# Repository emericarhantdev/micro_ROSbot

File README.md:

# PAMI Power Board (KiCad)

Power/IO board for a Small MicroROS-based robot project. Contains KiCad schematics/PCB, custom symbols/footprints, and fabrication outputs (Gerbers + drills).

## Contents
- PAMI-Power_Board.kicad_pro / .kicad_sch / .kicad_pcb: main KiCad project
- FAB/: manufacturing files (Gerbers, PTH/NPTH drills, job file)
- Specific_symbols_and_footprints/: custom symbols/footprints + 3D models
- top_level_diagrams/: high-level diagrams

## Board routing stage

## Final board result

## Fabrication
Upload the files in FAB/ (Gerbers + drills) to your PCB manufacturer.

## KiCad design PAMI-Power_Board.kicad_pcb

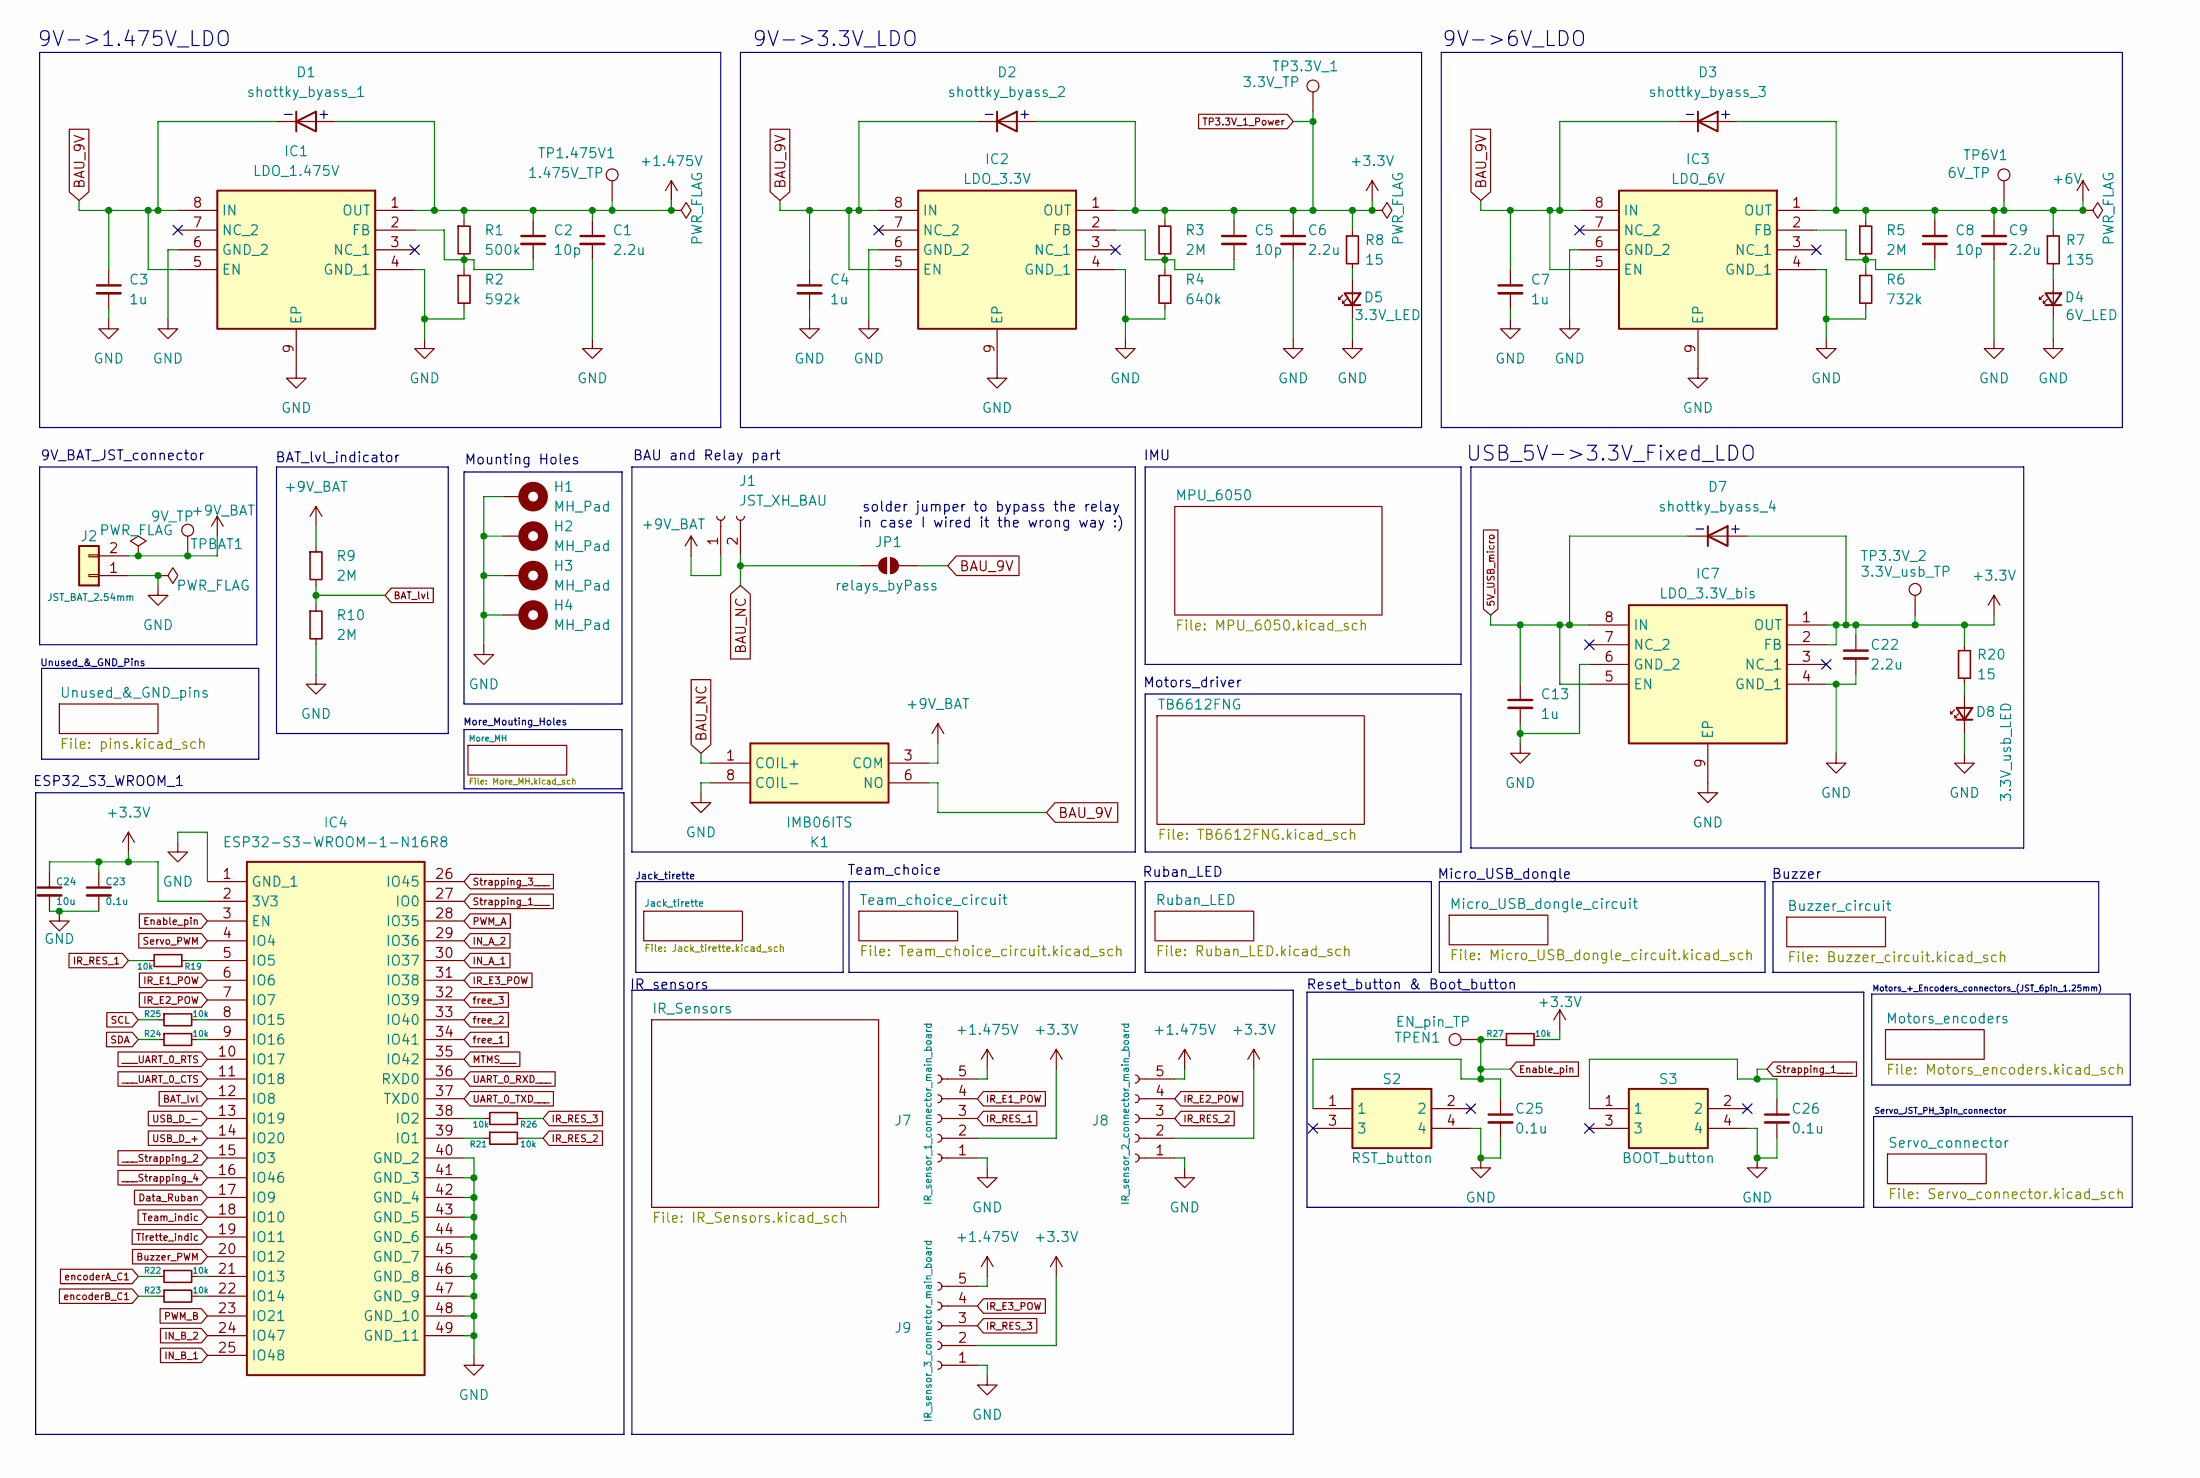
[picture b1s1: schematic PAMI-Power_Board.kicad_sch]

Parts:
C1, C6, C9, C22: 2.2u; C_0805_2012Metric_Pad1.18x1.45mm_HandSolder
C2, C5, C8: 10p; C_0805_2012Metric_Pad1.18x1.45mm_HandSolder
C3, C4, C7, C13: 1u; C_0805_2012Metric_Pad1.18x1.45mm_HandSolder
C23, C25, C26: 0.1u; C_0805_2012Metric_Pad1.18x1.45mm_HandSolder
C24: 10u; C_0805_2012Metric_Pad1.18x1.45mm_HandSolder
D1: shottky_byass_1; SOD2512X113N
D2: shottky_byass_2; SOD2512X113N
D3: shottky_byass_3; SOD2512X113N
D4: 6V_LED; ASCKCG00NW5X5020302
D5: 3.3V_LED; ASCKCG00NW5X5020302
D7: shottky_byass_4; SOD2512X113N
D8: 3.3V_usb_LED; ASCKCG00NW5X5020302
H1, H2, H3, H4: MH_Pad; MountingHole_2.2mm_M2_Pad_Via
IC1: LDO_1.475V; SOP65P490X110-9N; Manufacturer_Part_Number TLV76701DGNR; Mouser Part Number 595-TLV76701DGNR
IC2: LDO_3.3V; SOP65P490X110-9N; Manufacturer_Part_Number TLV76701DGNR; Mouser Part Number 595-TLV76701DGNR
IC3: LDO_6V; SOP65P490X110-9N; Manufacturer_Part_Number TLV76701DGNR; Mouser Part Number 595-TLV76701DGNR
IC4: ESP32-S3-WROOM-1-N16R8; ESP32S3WROOM1N16R8; Manufacturer_Part_Number ESP32-S3-WROOM-1-N16R8; Mouser Part Number 356-ESP32S3WRM1N16R8
IC7: LDO_3.3V_bis; SOP65P490X110-9N; Manufacturer_Part_Number TLV76701DGNR; Mouser Part Number 595-TLV76701DGNR
J1: JST_XH_BAU; JST_XH_B2B-XH-A_1x02_P2.50mm_Vertical
J2: JST_BAT_2.54mm; JST_XH_B2B-XH-A_1x02_P2.50mm_Vertical
J7: IR_sensor_1_connector_main_board; JST_ZH_1x05_P1.50mm_Vertical
J8: IR_sensor_2_connector_main_board; JST_ZH_1x05_P1.50mm_Vertical
J9: IR_sensor_3_connector_main_board; JST_ZH_1x05_P1.50mm_Vertical
JP1: relays_byPass; SolderJumper-2_P1.3mm_Open_Pad1.0x1.5mm
K1: IMB06ITS; IMB03ITS; Manufacturer_Part_Number IMB03ITS; Mouser Part Number 655-IMB03ITS
R1: 500k; R_0805_2012Metric_Pad1.20x1.40mm_HandSolder
R2: 592k; R_0805_2012Metric_Pad1.20x1.40mm_HandSolder
R3, R5, R9, R10: 2M; R_0805_2012Metric_Pad1.20x1.40mm_HandSolder
R4: 640k; R_0805_2012Metric_Pad1.20x1.40mm_HandSolder
R6: 732k; R_0805_2012Metric_Pad1.20x1.40mm_HandSolder
R7: 135; R_0805_2012Metric_Pad1.20x1.40mm_HandSolder
R8, R20: 15; R_0805_2012Metric_Pad1.20x1.40mm_HandSolder
R19, R21, R22, R23, R24, R25, R26, R27: 10k; R_0805_2012Metric_Pad1.20x1.40mm_HandSolder
S2: RST_button; PTS810SJG250SMTRLFS; Manufacturer_Part_Number PTS810SJM250SMTRLFS; Mouser Part Number 611-PTS810SJM250SMTR
S3: BOOT_button; PTS810SJG250SMTRLFS; Manufacturer_Part_Number PTS810SJM250SMTRLFS; Mouser Part Number 611-PTS810SJM250SMTR
TP1.475V1: 1.475V_TP; S275146R
TP3.3V_1: 3.3V_TP; S275146R
TP3.3V_2: 3.3V_usb_TP; S275146R
TP6V1: 6V_TP; S275146R
TPBAT1: 9V_TP; S275146R
TPEN1: EN_pin_TP; S275146R

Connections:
5V_USB_micro: C13.1, D7.1 (K), IC7.5 (EN), IC7.8 (IN); also elsewhere on the board
+1.475V: C1.1, C2.1, D1.2 (A), IC1.1 (OUT), J7.5, J8.5, J9.5, R1.1, TP1.475V1.1; also elsewhere on the board
+6V: C8.1, C9.1, D3.2 (A), IC3.1 (OUT), R5.1, R7.1, TP6V1.1; also elsewhere on the board
+9V_BAT: J1.1, J2.2, K1.3 (COM), R9.1, TPBAT1.1
BAT_lvl: IC4.12 (IO8), R9.2, R10.1
BAU_9V: C3.1, C4.1, C7.1, D1.1 (K), D2.1 (K), D3.1 (K), IC1.5 (EN), IC1.8 (IN), IC2.5 (EN), IC2.8 (IN), IC3.5 (EN), IC3.8 (IN), JP1.2 (B), K1.6 (NO)
BAU_NC: J1.2, JP1.1 (A), K1.1 (COIL+)
Buzzer_PWM: IC4.20 (IO12); also elsewhere on the board
Data_Ruban: IC4.17 (IO9); also elsewhere on the board
Enable_pin: C25.1, IC4.3 (EN), R27.1, S2.1, TPEN1.1
GND: C1.2, C3.2, C4.2, C6.2, C7.2, C9.2, C13.2, C22.2, C23.2, C24.2, C25.2, C26.2, D4.1 (K), D5.1 (K), D8.1 (K), H1.1, H2.1, H3.1, H4.1, IC1.4 (GND_1), IC1.6 (GND_2), IC1.9 (EP), IC2.4 (GND_1), IC2.6 (GND_2), IC2.9 (EP), IC3.4 (GND_1), IC3.6 (GND_2), IC3.9 (EP), IC4.1 (GND_1), IC4.40 (GND_2), IC4.41 (GND_3), IC4.42 (GND_4), IC4.43 (GND_5), IC4.44 (GND_6), IC4.45 (GND_7), IC4.46 (GND_8), IC4.47 (GND_9), IC4.48 (GND_10), IC4.49 (GND_11), IC7.4 (GND_1), IC7.6 (GND_2), IC7.9 (EP), J2.1, J7.1, J8.1, J9.1, K1.8 (COIL-), R2.2, R4.2, R6.2, R10.2, S2.4, S3.4; also elsewhere on the board
IN_A_1: IC4.30 (IO37); also elsewhere on the board
IN_A_2: IC4.29 (IO36); also elsewhere on the board
IN_B_1: IC4.25 (IO48); also elsewhere on the board
IN_B_2: IC4.24 (IO47); also elsewhere on the board
IR_E1_POW: IC4.6 (IO6), J7.4; also elsewhere on the board
IR_E2_POW: IC4.7 (IO7), J8.4; also elsewhere on the board
IR_E3_POW: IC4.31 (IO38), J9.4; also elsewhere on the board
IR_RES_1: J7.3, R19.2; also elsewhere on the board
IR_RES_2: J8.3, R21.2; also elsewhere on the board
IR_RES_3: J9.3, R26.1; also elsewhere on the board
MTMS___: IC4.35 (IO42); also elsewhere on the board
unnamed: D4.2 (A), R7.2
unnamed: D5.2 (A), R8.2
unnamed: D8.2 (A), R20.2
unnamed: C2.2, IC1.2 (FB), R1.2, R2.1
unnamed: C5.2, IC2.2 (FB), R3.2, R4.1
unnamed: C8.2, IC3.2 (FB), R5.2, R6.1
unnamed: IC4.39 (IO1), R21.1
unnamed: IC4.38 (IO2), R26.2
unnamed: IC4.5 (IO5), R19.1
unnamed: IC4.21 (IO13), R22.2
unnamed: IC4.22 (IO14), R23.2
unnamed: IC4.8 (IO15), R25.2
unnamed: IC4.9 (IO16), R24.2
PWM_A: IC4.28 (IO35); also elsewhere on the board
PWM_B: IC4.23 (IO21); also elsewhere on the board
SCL: R25.1; also elsewhere on the board
SDA: R24.1; also elsewhere on the board
Servo_PWM: IC4.4 (IO4); also elsewhere on the board
Strapping_1___: C26.1, IC4.27 (IO0), S3.1
Strapping_3___: IC4.26 (IO45); also elsewhere on the board
TP3.3V_1_Power: C5.1, C6.1, C22.1, C23.1, C24.1, D2.2 (A), D7.2 (A), IC2.1 (OUT), IC4.2 (3V3), IC7.1 (OUT), IC7.2 (FB), J7.2, J8.2, J9.2, R3.1, R8.1, R20.1, R27.2, TP3.3V_1.1, TP3.3V_2.1; also elsewhere on the board
Team_indic: IC4.18 (IO10); also elsewhere on the board
Tirette_indic: IC4.19 (IO11); also elsewhere on the board
UART_0_RXD___: IC4.36 (RXD0); also elsewhere on the board
UART_0_TXD___: IC4.37 (TXD0); also elsewhere on the board
USB_D_+: IC4.14 (IO20); also elsewhere on the board
USB_D_-: IC4.13 (IO19); also elsewhere on the board
___Strapping_2: IC4.15 (IO3); also elsewhere on the board
___Strapping_4: IC4.16 (IO46); also elsewhere on the board
___UART_0_CTS: IC4.11 (IO18); also elsewhere on the board
___UART_0_RTS: IC4.10 (IO17); also elsewhere on the board
encoderA_C1: R22.1; also elsewhere on the board
encoderB_C1: R23.1; also elsewhere on the board
free_1: IC4.34 (IO41); also elsewhere on the board
free_2: IC4.33 (IO40); also elsewhere on the board
free_3: IC4.32 (IO39); also elsewhere on the board

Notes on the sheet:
9V->6V_LDO
Motors_driver
USB_5V->3.3V_Fixed_LDO
Servo_JST_PH_3pin_connector
solder jumper to bypass the relay in case I wired it the wrong way :)
Ruban_LED
BAU and Relay part
IR_sensors
9V->1.475V_LDO
IMU
9V_BAT_JST_connector
Team_choice
ESP32_S3_WROOM_1
Jack_tirette
Motors_+_Encoders_connectors_(JST_6pin_1.25mm)
Mounting Holes
9V->3.3V_LDO
Micro_USB_dongle
BAT_lvl_indicator
Buzzer
More_Mouting_Holes
Unused_&_GND_Pins
Reset_button & Boot_button

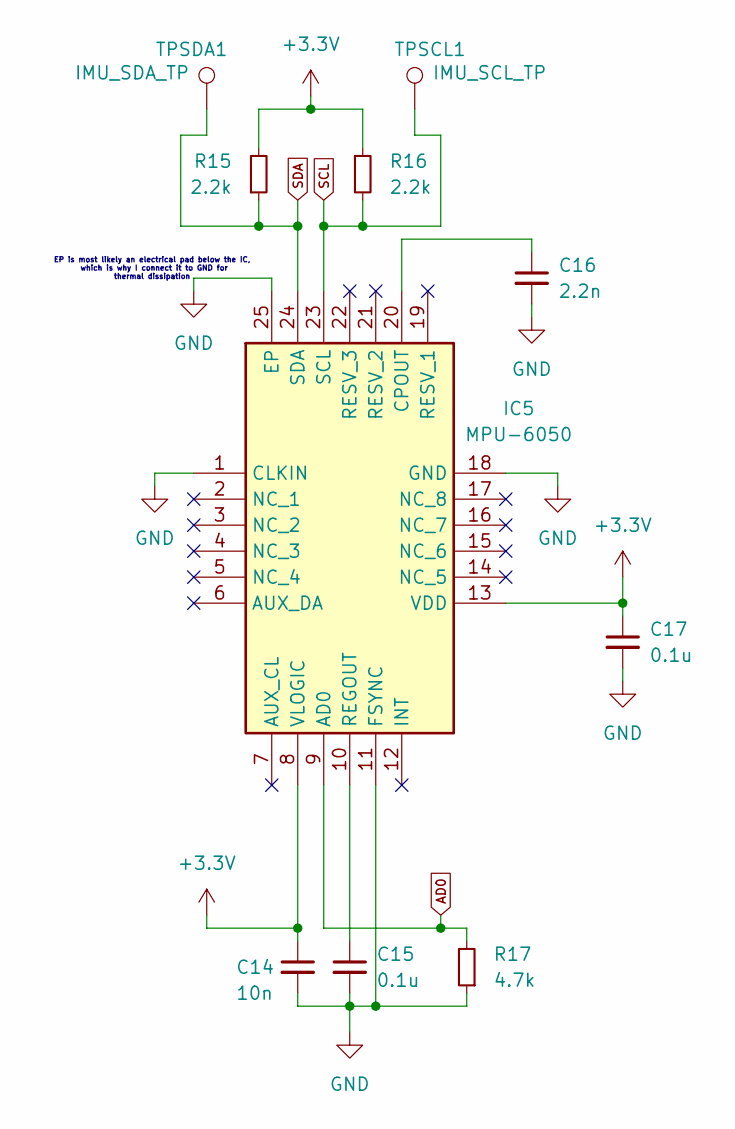
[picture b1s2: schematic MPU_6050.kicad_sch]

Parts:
C14: 10n; C_0805_2012Metric_Pad1.18x1.45mm_HandSolder
C15, C17: 0.1u; C_0805_2012Metric_Pad1.18x1.45mm_HandSolder
C16: 2.2n; C_0805_2012Metric_Pad1.18x1.45mm_HandSolder
IC5: MPU-6050; MPU6050; Manufacturer_Part_Number MPU-6050; Mouser Part Number 410-MPU-6050
R15, R16: 2.2k; R_0805_2012Metric_Pad1.20x1.40mm_HandSolder
R17: 4.7k; R_0805_2012Metric_Pad1.20x1.40mm_HandSolder
TPSCL1: IMU_SCL_TP; S275146R
TPSDA1: IMU_SDA_TP; S275146R

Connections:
AD0: IC5.9 (AD0), R17.2
GND: C14.2, C15.2, C16.2, C17.2, IC5.1 (CLKIN), IC5.11 (FSYNC), IC5.18 (GND), IC5.25 (EP), R17.1; also elsewhere on the board
unnamed: C16.1, IC5.20 (CPOUT)
unnamed: C15.1, IC5.10 (REGOUT)
SCL: IC5.23 (SCL), R16.2, TPSCL1.1; also elsewhere on the board
SDA: IC5.24 (SDA), R15.1, TPSDA1.1; also elsewhere on the board
TP3.3V_1_Power: C14.1, C17.1, IC5.8 (VLOGIC), IC5.13 (VDD), R15.2, R16.1; also elsewhere on the board

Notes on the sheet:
EP is most likely an electrical pad below the IC, which is why I connect it to GND for thermal dissipation

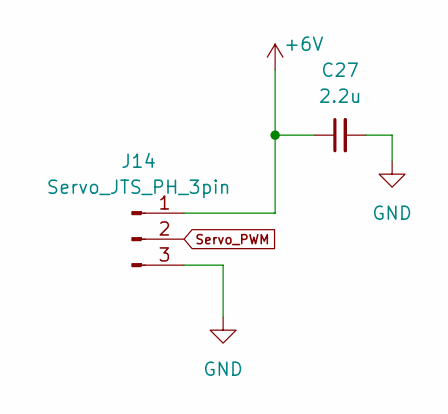
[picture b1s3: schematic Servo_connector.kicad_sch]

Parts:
C27: 2.2u; C_0805_2012Metric_Pad1.18x1.45mm_HandSolder
J14: Servo_JTS_PH_3pin; JST_PH_B3B-PH-K_1x03_P2.00mm_Vertical

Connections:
+6V: C27.1, J14.1; also elsewhere on the board
GND: C27.2, J14.3; also elsewhere on the board
Servo_PWM: J14.2; also elsewhere on the board

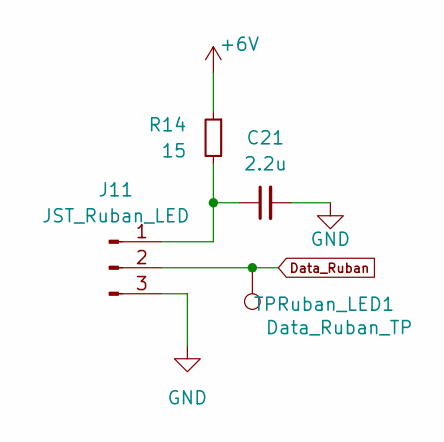
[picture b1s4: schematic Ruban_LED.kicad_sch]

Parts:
C21: 2.2u; C_0805_2012Metric_Pad1.18x1.45mm_HandSolder
J11: JST_Ruban_LED; JST_PH_B3B-PH-K_1x03_P2.00mm_Vertical
R14: 15; R_0805_2012Metric_Pad1.20x1.40mm_HandSolder
TPRuban_LED1: Data_Ruban_TP; S275146R

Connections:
+6V: R14.1; also elsewhere on the board
Data_Ruban: J11.2, TPRuban_LED1.1; also elsewhere on the board
GND: C21.2, J11.3; also elsewhere on the board
unnamed: C21.1, J11.1, R14.2

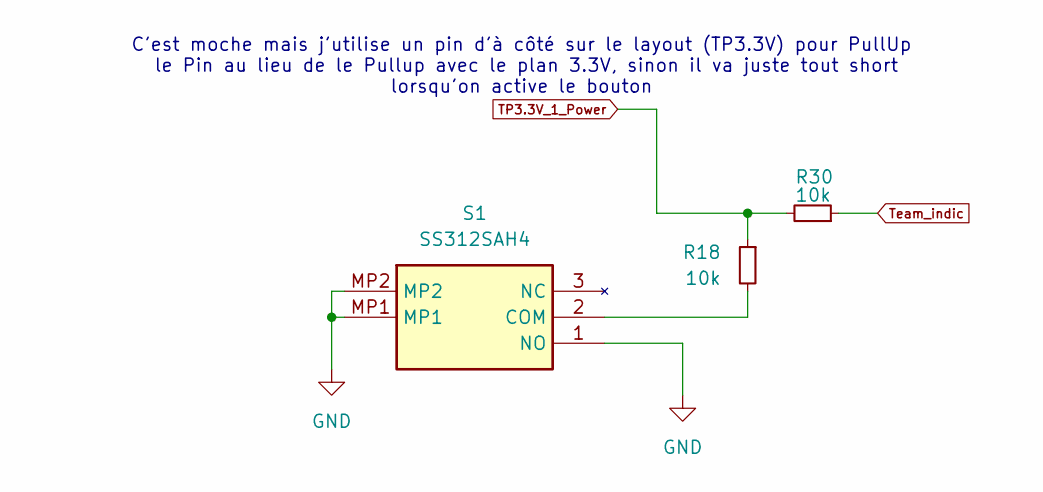
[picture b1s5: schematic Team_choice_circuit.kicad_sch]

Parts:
R18, R30: 10k; R_0805_2012Metric_Pad1.20x1.40mm_HandSolder
S1: SS312SAH4; Manufacturer_Part_Number SS312SAH4; Mouser Part Number 633-SS312SAH4

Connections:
GND: S1.1 (NO), S1.MP1, S1.MP2; also elsewhere on the board
unnamed: R18.2, S1.2 (COM)
TP3.3V_1_Power: R18.1, R30.2; also elsewhere on the board
Team_indic: R30.1; also elsewhere on the board

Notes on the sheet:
C'est moche mais j'utilise un pin d'à côté sur le layout (TP3.3V) pour PullUp le Pin au lieu de le Pullup avec le plan 3.3V, sinon il va juste tout short lorsqu'on active le bouton

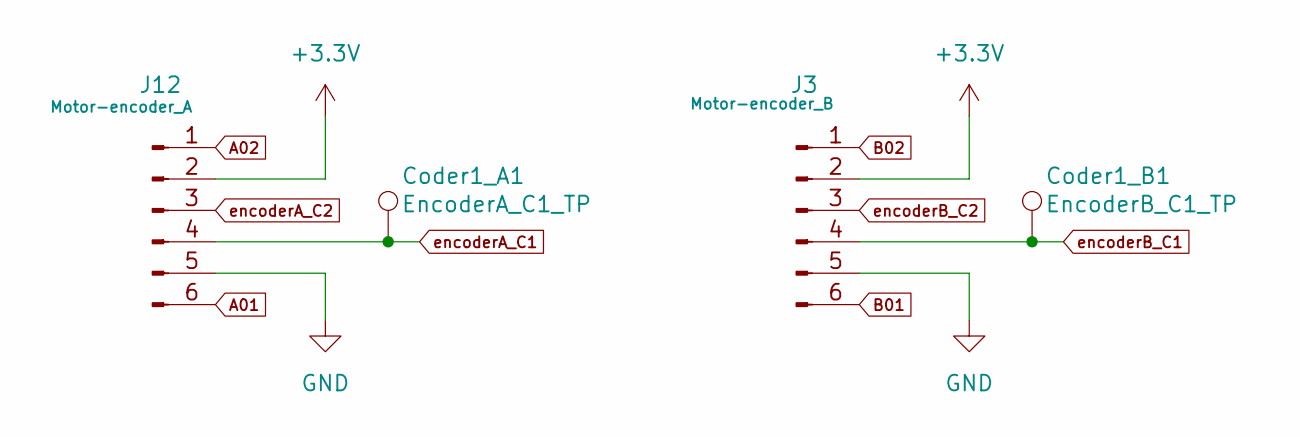
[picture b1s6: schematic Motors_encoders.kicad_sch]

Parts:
Coder1_A1: EncoderA_C1_TP; S275146R
Coder1_B1: EncoderB_C1_TP; S275146R
J3: Motor-encoder_B; JST_ZH_1x06_P1.5mm_no_Connector
J12: Motor-encoder_A; JST_ZH_1x06_P1.5mm_no_Connector

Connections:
A01: J12.6; also elsewhere on the board
A02: J12.1; also elsewhere on the board
B01: J3.6; also elsewhere on the board
B02: J3.1; also elsewhere on the board
GND: J3.5, J12.5; also elsewhere on the board
TP3.3V_1_Power: J3.2, J12.2; also elsewhere on the board
encoderA_C1: Coder1_A1.1, J12.4; also elsewhere on the board
encoderA_C2: J12.3
encoderB_C1: Coder1_B1.1, J3.4; also elsewhere on the board
encoderB_C2: J3.3

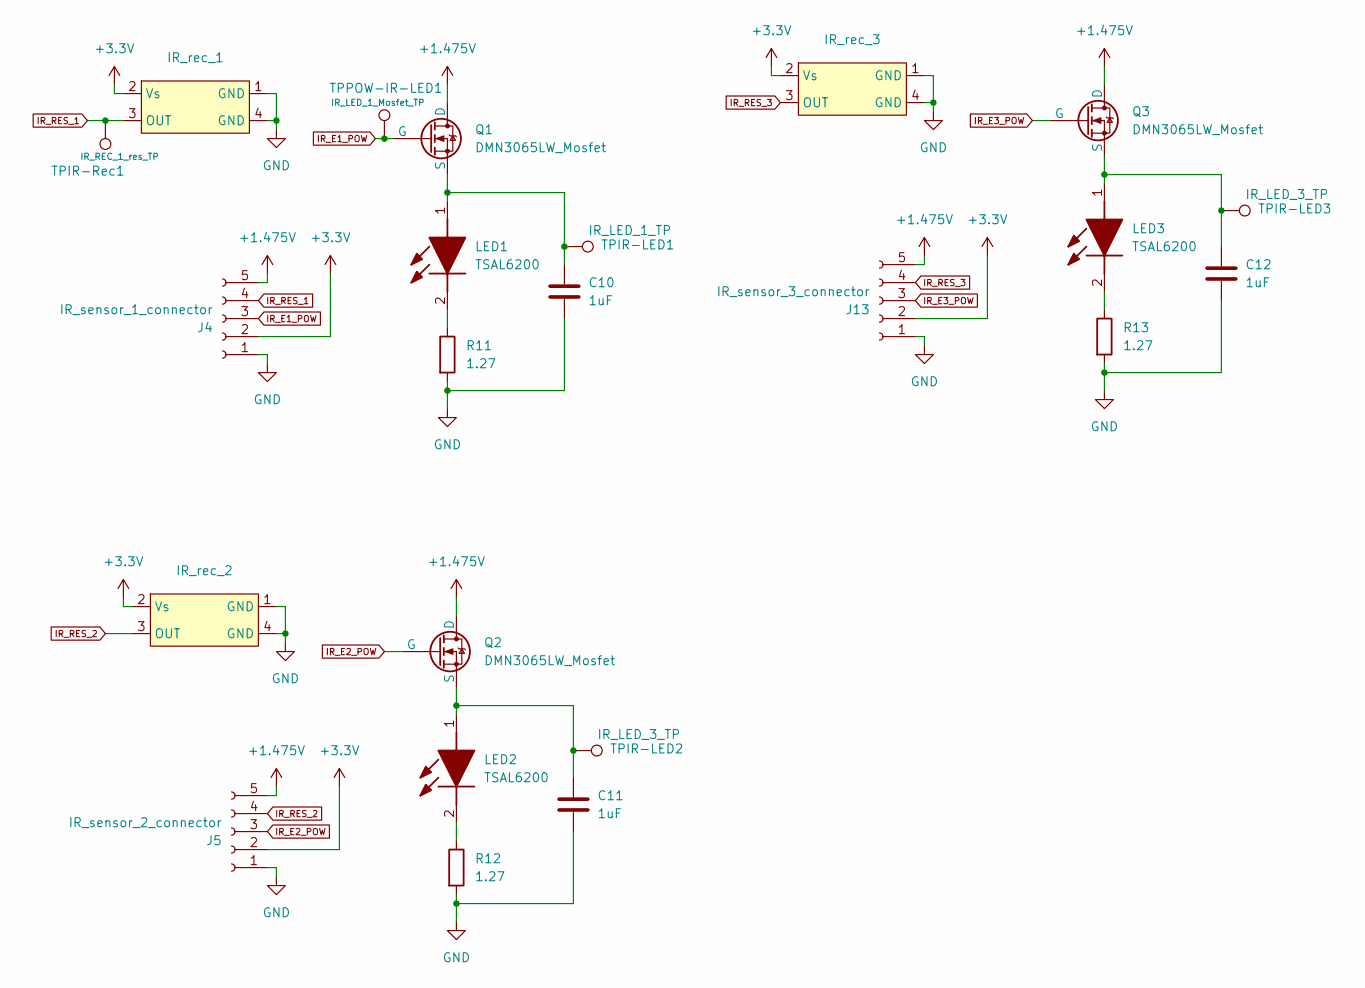
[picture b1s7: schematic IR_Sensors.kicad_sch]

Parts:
C10, C11, C12: 1uF; C_0805_2012Metric_Pad1.18x1.45mm_HandSolder
IR_rec_1, IR_rec_2, IR_rec_3: IR_receiver_TSSP77038TT
J4: IR_sensor_1_connector; JST_ZH_1x05_P1.50mm_Vertical
J5: IR_sensor_2_connector; JST_ZH_1x05_P1.50mm_Vertical
J13: IR_sensor_3_connector; JST_ZH_1x05_P1.50mm_Vertical
LED1, LED2, LED3: TSAL6200; Manufacturer_Part_Number TSAL6200; Mouser Part Number 782-TSAL6200
Q1, Q2, Q3: DMN3065LW_Mosfet; SOT65P210X110-3N
R11, R12, R13: 1.27; R_0805_2012Metric_Pad1.20x1.40mm_HandSolder
TPIR-LED1: IR_LED_1_TP; S275146R
TPIR-LED2, TPIR-LED3: IR_LED_3_TP; S275146R
TPIR-Rec1: IR_REC_1_res_TP; S275146R
TPPOW-IR-LED1: IR_LED_1_Mosfet_TP; S275146R

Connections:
+1.475V: J4.5, J5.5, J13.5, Q1.1 (D), Q2.1 (D), Q3.1 (D); also elsewhere on the board
GND: C10.2, C11.2, C12.2, IR_rec_1.1 (GND), IR_rec_1.4 (GND), IR_rec_2.1 (GND), IR_rec_2.4 (GND), IR_rec_3.1 (GND), IR_rec_3.4 (GND), J4.1, J5.1, J13.1, R11.2, R12.2, R13.2; also elsewhere on the board
IR_E1_POW: J4.3, Q1.2 (G), TPPOW-IR-LED1.1; also elsewhere on the board
IR_E2_POW: J5.3, Q2.2 (G); also elsewhere on the board
IR_E3_POW: J13.3, Q3.2 (G); also elsewhere on the board
IR_RES_1: IR_rec_1.3 (OUT), J4.4, TPIR-Rec1.1; also elsewhere on the board
IR_RES_2: IR_rec_2.3 (OUT), J5.4; also elsewhere on the board
IR_RES_3: IR_rec_3.3 (OUT), J13.4; also elsewhere on the board
unnamed: C10.1, LED1.1 (A), Q1.3 (S), TPIR-LED1.1
unnamed: LED1.2 (K), R11.1
unnamed: C11.1, LED2.1 (A), Q2.3 (S), TPIR-LED2.1
unnamed: LED2.2 (K), R12.1
unnamed: C12.1, LED3.1 (A), Q3.3 (S), TPIR-LED3.1
unnamed: LED3.2 (K), R13.1
TP3.3V_1_Power: IR_rec_1.2 (Vs), IR_rec_2.2 (Vs), IR_rec_3.2 (Vs), J4.2, J5.2, J13.2; also elsewhere on the board

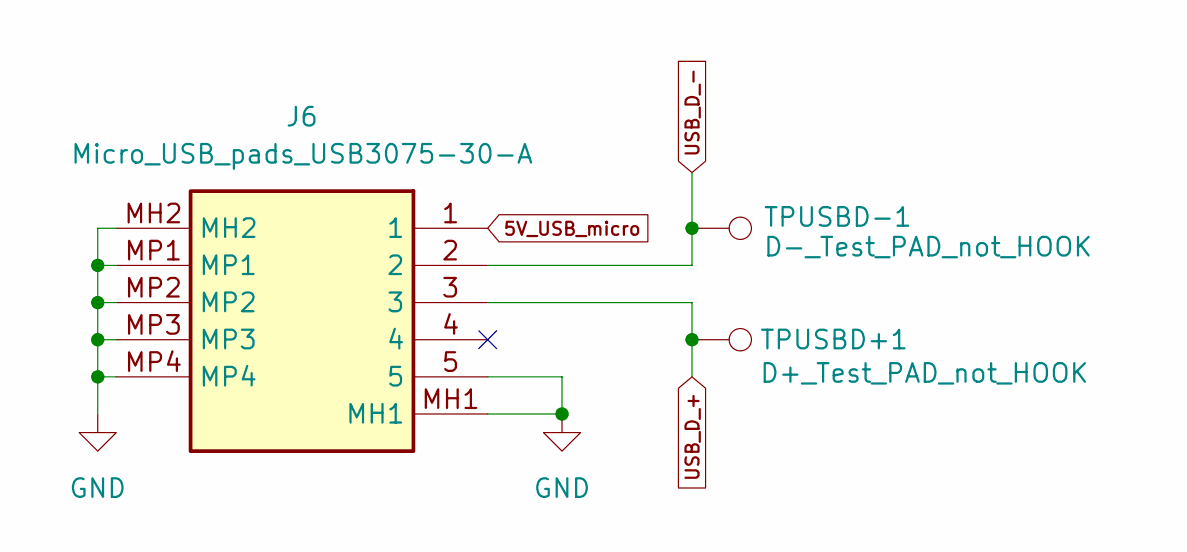
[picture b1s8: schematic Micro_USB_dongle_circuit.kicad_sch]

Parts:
J6: Micro_USB_pads_USB3075-30-A; USB307530A; Manufacturer_Part_Number USB3075-30-A; Mouser Part Number 640-USB3075-30-A
TPUSBD+1: D+_Test_PAD_not_HOOK; TestPoint_Pad_D2.0mm
TPUSBD-1: D-_Test_PAD_not_HOOK; TestPoint_Pad_D2.0mm

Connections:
5V_USB_micro: J6.1; also elsewhere on the board
GND: J6.5, J6.MH1, J6.MH2, J6.MP1, J6.MP2, J6.MP3, J6.MP4; also elsewhere on the board
USB_D_+: J6.3, TPUSBD+1.1; also elsewhere on the board
USB_D_-: J6.2, TPUSBD-1.1; also elsewhere on the board

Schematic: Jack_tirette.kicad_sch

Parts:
J20: JST_Jack_2.54mm; JST_XH_B2B-XH-A_1x02_P2.50mm_Vertical
R29, R31: 10k; R_0805_2012Metric_Pad1.20x1.40mm_HandSolder
Tirette1: tirette_TP; S275146R

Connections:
GND: J20.1; also elsewhere on the board
unnamed: J20.2, R29.2
TP3.3V_1_Power: R29.1, R31.2; also elsewhere on the board
Tirette_indic: R31.1, Tirette1.1; also elsewhere on the board

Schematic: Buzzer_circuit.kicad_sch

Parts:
LS1: CMT-0525-75-SMT-TR; CMT052575SMTTR; Manufacturer_Part_Number CMT-0525-75-SMT-TR; Mouser Part Number 490-CMT-0525-75SMTTR
Q4: DMN3065LW-7; SOT65P210X110-3N
R28: 3; R_0805_2012Metric_Pad1.20x1.40mm_HandSolder
TPBuzzer1: Buzzer_PWM_TP; S275146R

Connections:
Buzzer_PWM: Q4.2 (G), TPBuzzer1.1; also elsewhere on the board
GND: LS1.2 (-); also elsewhere on the board
unnamed: LS1.1 (+), Q4.3 (S)
unnamed: Q4.1 (D), R28.2
TP3.3V_1_Power: R28.1; also elsewhere on the board

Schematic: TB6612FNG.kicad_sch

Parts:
C18, C20: 0.1u; C_0805_2012Metric_Pad1.18x1.45mm_HandSolder
C19: 220u; CAPPM3528X210N
IC6: TB6612FNG,C,8,EL; SOP65P760X160-24N; Manufacturer_Part_Number TB6612FNG,C,8,EL; Mouser Part Number 757-TB6612FNGC8EL
PWM-A1: PWM_B_TP; S275146R
TPPWM-B1: PWM_B_TP; S275146R

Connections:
+6V: C18.2, C19.1, IC6.13 (VM2), IC6.14 (VM3), IC6.24 (VM1); also elsewhere on the board
A01: IC6.5 (AO2_1), IC6.6 (AO2_2); also elsewhere on the board
A02: IC6.1 (AO1_1), IC6.2 (AO1_2); also elsewhere on the board
B01: IC6.11 (BO1_1), IC6.12 (BO1_2); also elsewhere on the board
B02: IC6.7 (BO2_1), IC6.8 (BO2_2); also elsewhere on the board
GND: C18.1, C19.2, C20.2, IC6.3 (PGND1_1), IC6.4 (PGND1_2), IC6.9 (PGND2_1), IC6.10 (PGND2_2), IC6.18 (GND); also elsewhere on the board
IN_A_1: IC6.21 (AIN1); also elsewhere on the board
IN_A_2: IC6.22 (AIN2); also elsewhere on the board
IN_B_1: IC6.17 (BIN1); also elsewhere on the board
IN_B_2: IC6.16 (BIN2); also elsewhere on the board
PWM_A: IC6.23 (PWMA), PWM-A1.1; also elsewhere on the board
PWM_B: IC6.15 (PWMB), TPPWM-B1.1; also elsewhere on the board
TP3.3V_1_Power: C20.1, IC6.19 (STBY), IC6.20 (VCC); also elsewhere on the board

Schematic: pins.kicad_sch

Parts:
J10: unused_pin_3; PinSocket_1x07_P2.54mm_Vertical
J15: unused_pin_2; PinSocket_1x02_P2.54mm_Vertical
J16: GND_Pins; PinSocket_1x04_P2.54mm_Vertical
J17: unused_pin_1; PinSocket_1x03_P2.54mm_Vertical

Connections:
GND: J16.3, J16.4, J17.1; also elsewhere on the board
MTMS___: J10.3; also elsewhere on the board
Strapping_3___: J10.7; also elsewhere on the board
TP3.3V_1_Power: J16.1, J16.2; also elsewhere on the board
UART_0_RXD___: J10.2; also elsewhere on the board
UART_0_TXD___: J10.1; also elsewhere on the board
___Strapping_2: J17.2; also elsewhere on the board
___Strapping_4: J17.3; also elsewhere on the board
___UART_0_CTS: J15.1; also elsewhere on the board
___UART_0_RTS: J15.2; also elsewhere on the board
free_1: J10.4; also elsewhere on the board
free_2: J10.5; also elsewhere on the board
free_3: J10.6; also elsewhere on the board

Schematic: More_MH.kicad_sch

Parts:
H5, H6, H7, H8, H9, H10: MH_Pad; MountingHole_2.2mm_M2_Pad_Via

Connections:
GND: H5.1, H6.1, H7.1, H8.1, H9.1, H10.1; also elsewhere on the board

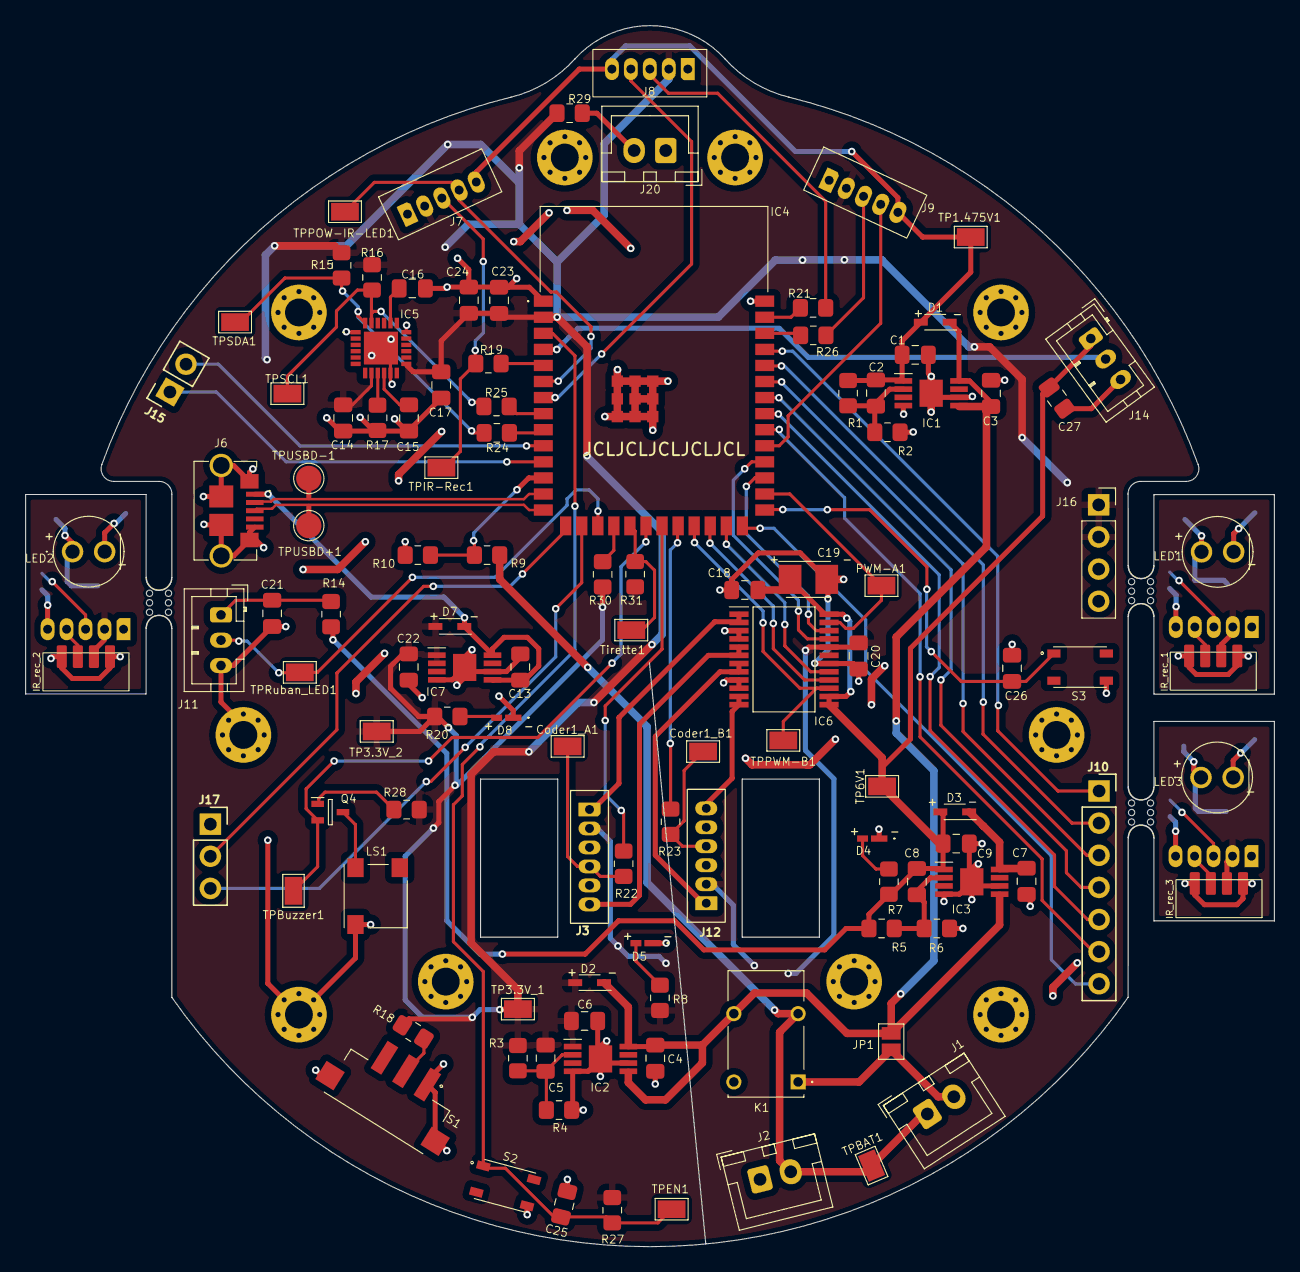
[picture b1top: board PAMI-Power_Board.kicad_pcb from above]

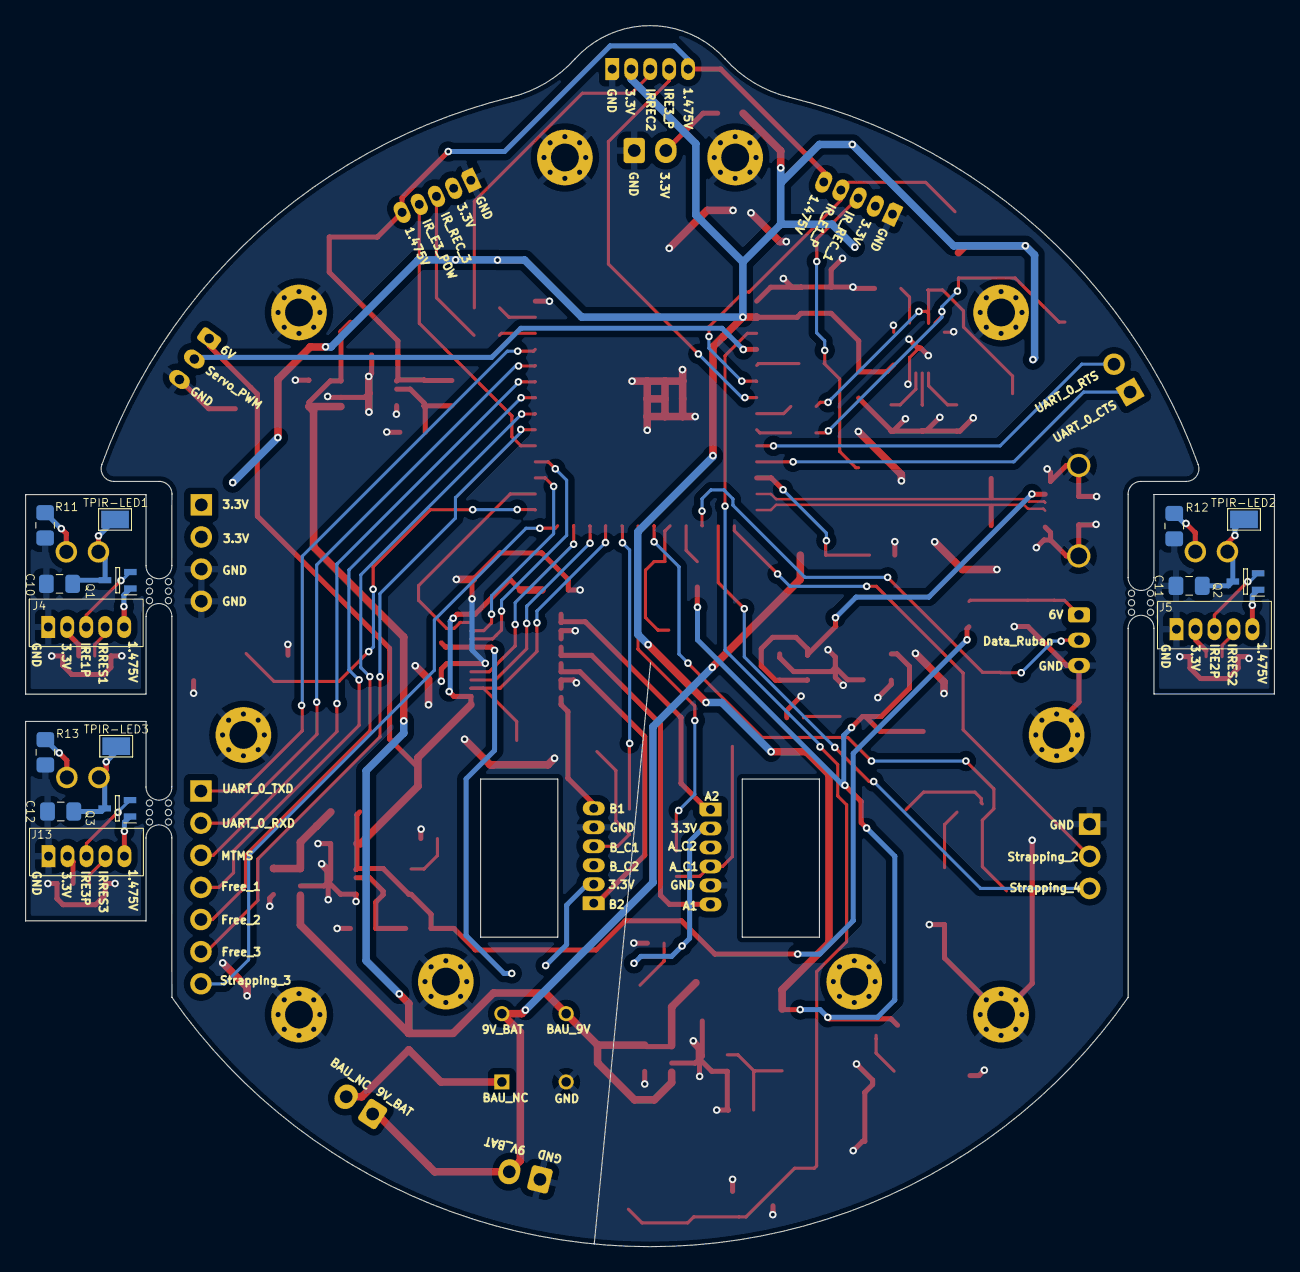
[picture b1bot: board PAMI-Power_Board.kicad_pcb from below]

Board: 2 copper layers, 98.7 x 96.5 mm, 141 parts (15 on the bottom side), 76 nets.

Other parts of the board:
mouse-bite-2mm-slot, mouse-bite-2mm-slot#2, mouse-bite-2mm-slot#3: VAL**; mouse-bite-2mm-slot

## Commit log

2026-02-18 added all Board Schematics
2026-02-18 Initialize README with project information
    Added project details, contents, and fabrication instructions.
